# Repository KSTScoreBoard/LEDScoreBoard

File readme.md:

# LED得点掲示板 2023ver.

# 準備するもの
- 電源装置(DC 40V / 300W程度) x4
- 制御基板 x4
- 制御基板用フック x4
- ACアダプタ(5V) x4
- LEDパネル x12
- 電源ケーブル x4
- Wi-Fiアクセスポイント(Windowsのモバイルホットスポット/携帯のテザリング　等) x1
- 操作用端末(Chromeブラウザが動けばOK) x1

# 準備
## 電源
長い間電源を使っていなかった場合は、LEDに繋ぐ前に電源の電圧が39~40Vの範囲にあるかをテスターを使って確認してください。  

## Wi-Fiアクセスポイント
Windowsのモバイルホットスポット/携帯のテザリングとうで制御基板が接続するためのアクセスポイントを用意してください。

# 組み立て
1. 各ブロックLEDパネル3枚を窓とアルミの柱の間に入れて固定する
2. 真ん中のパネル付近に制御基板を取り付ける。このとき基板裏のファンがケーブル等と干渉しないように注意する
3. 制御基板とLEDパネルを接続する
4. 電源装置と制御基板を接続する（電源はまだ入れない）

# 起動
1. 制御基板にACアダプタを接続する
2. 制御基板の起動とネットワーク接続を確認する。(auth ok,ready)と表示されていればOK
3. 電源装置とコンセントを接続する。　※コンセントは2系統から分割して電源をとること。
4. 制御アプリで「送信」を押す or 制御基板のボタンを押す　でLEDが点灯することを確認する
5. 得点「888」を表示してすべてのセグメントが点灯していることを確認する

# 操作

## 送信

各操作を行ったら送信ボタンを押してデータをLEDパネルへ送信してください。4つのブロックの状態を一斉に変更します。

## 得点を変える

各桁の上下にある「＋」、「－」ボタンで数字を操作して目的の得点に変更出来たら最後にページ上部の「送信」ボタンを押してください。また、複数のブロックの得点を同時に変更する場合は各ブロックの得点を操作し終わってから最後にまとめて「送信」を押してください。

## 明るさを変える

スライドバー（8段階）を一番左で消灯、一番右で明るさ最大です。

## 得点を隠す

得点発表時などに得点を隠すには「非表示」ボタンを使用します。3つのボタンが各桁に対応しており、推すとグレーになります。ボタンがグレーになった状態で「送信」することで非表示が押されてる桁は数字を隠せます。

# 詳細
## Wi-Fiについて
Wi-Fiは使用しているマイコンの関係で2.4Ghz帯を使用する必要があります。校舎に飛んでいるWi-FIは5Ghzのため、Windwosの「モバイルホットスポット」等の機能を使って2.4Ghzネットワークを用意してください。SSIDとパスワードは任意で、変更する場合はマイコンのプログラムも変更してください。

## マイコンの設定情報について
通信に使用するIDとWi-Fi設定はメインのプログラムとは別のファイル **defines.h** に書き込まれています。プログラムを変更する場合は以下にソースコードがあるのでコピーしてください
<details><summary>defines.h</summary>

```
#ifndef defines_h
#define defines_h

#if !( defined(ESP8266) ||  defined(ESP32) )
#error This code is intended to run on the ESP32 platform! Please check your Tools->Board setting.
#elif ( ARDUINO_ESP32S2_DEV || ARDUINO_FEATHERS2 || ARDUINO_ESP32S2_THING_PLUS || ARDUINO_MICROS2 || \
        ARDUINO_METRO_ESP32S2 || ARDUINO_MAGTAG29_ESP32S2 || ARDUINO_FUNHOUSE_ESP32S2 || \
        ARDUINO_ADAFRUIT_FEATHER_ESP32S2_NOPSRAM )
#define BOARD_TYPE      "ESP32-S2"
#elif ( ARDUINO_ESP32C3_DEV )
#warning Using ESP32-C3 boards
#define BOARD_TYPE      "ESP32-C3"
#else
#define BOARD_TYPE      "ESP32"
#endif

#ifndef BOARD_NAME
  #define BOARD_NAME    BOARD_TYPE
#endif

#define DEBUG_WEBSOCKETS_PORT     Serial
// Debug Level from 0 to 4
#define _WEBSOCKETS_LOGLEVEL_     3

const char* ssid = "your ssid";          //Enter SSID
const char* password = "your passsword"; //Enter Password

const String identification = "1";       //Enter ID

// Deprecated echo.websocket.org to be replaced or it won't work
const char* websockets_connection_string = "wss://echo.websocket.org/"; //Enter server adress

// KH, This certificate was updated 15.04.2021,
// Issued on Mar 15th 2021, expired on June 13th 2021
const char echo_org_ssl_ca_cert[] PROGMEM = \
                                            "-----BEGIN CERTIFICATE-----\n" \
                                            "MIIEZTCCA02gAwIBAgIQQAF1BIMUpMghjISpDBbN3zANBgkqhkiG9w0BAQsFADA/\n" \
                                            "MSQwIgYDVQQKExtEaWdpdGFsIFNpZ25hdHVyZSBUcnVzdCBDby4xFzAVBgNVBAMT\n" \
                                            "DkRTVCBSb290IENBIFgzMB4XDTIwMTAwNzE5MjE0MFoXDTIxMDkyOTE5MjE0MFow\n" \
                                            "MjELMAkGA1UEBhMCVVMxFjAUBgNVBAoTDUxldCdzIEVuY3J5cHQxCzAJBgNVBAMT\n" \
                                            "AlIzMIIBIjANBgkqhkiG9w0BAQEFAAOCAQ8AMIIBCgKCAQEAuwIVKMz2oJTTDxLs\n" \
                                            "jVWSw/iC8ZmmekKIp10mqrUrucVMsa+Oa/l1yKPXD0eUFFU1V4yeqKI5GfWCPEKp\n" \
                                            "Tm71O8Mu243AsFzzWTjn7c9p8FoLG77AlCQlh/o3cbMT5xys4Zvv2+Q7RVJFlqnB\n" \
                                            "U840yFLuta7tj95gcOKlVKu2bQ6XpUA0ayvTvGbrZjR8+muLj1cpmfgwF126cm/7\n" \
                                            "gcWt0oZYPRfH5wm78Sv3htzB2nFd1EbjzK0lwYi8YGd1ZrPxGPeiXOZT/zqItkel\n" \
                                            "/xMY6pgJdz+dU/nPAeX1pnAXFK9jpP+Zs5Od3FOnBv5IhR2haa4ldbsTzFID9e1R\n" \
                                            "oYvbFQIDAQABo4IBaDCCAWQwEgYDVR0TAQH/BAgwBgEB/wIBADAOBgNVHQ8BAf8E\n" \
                                            "BAMCAYYwSwYIKwYBBQUHAQEEPzA9MDsGCCsGAQUFBzAChi9odHRwOi8vYXBwcy5p\n" \
                                            "ZGVudHJ1c3QuY29tL3Jvb3RzL2RzdHJvb3RjYXgzLnA3YzAfBgNVHSMEGDAWgBTE\n" \
                                            "p7Gkeyxx+tvhS5B1/8QVYIWJEDBUBgNVHSAETTBLMAgGBmeBDAECATA/BgsrBgEE\n" \
                                            "AYLfEwEBATAwMC4GCCsGAQUFBwIBFiJodHRwOi8vY3BzLnJvb3QteDEubGV0c2Vu\n" \
                                            "Y3J5cHQub3JnMDwGA1UdHwQ1MDMwMaAvoC2GK2h0dHA6Ly9jcmwuaWRlbnRydXN0\n" \
                                            "LmNvbS9EU1RST09UQ0FYM0NSTC5jcmwwHQYDVR0OBBYEFBQusxe3WFbLrlAJQOYf\n" \
                                            "r52LFMLGMB0GA1UdJQQWMBQGCCsGAQUFBwMBBggrBgEFBQcDAjANBgkqhkiG9w0B\n" \
                                            "AQsFAAOCAQEA2UzgyfWEiDcx27sT4rP8i2tiEmxYt0l+PAK3qB8oYevO4C5z70kH\n" \
                                            "ejWEHx2taPDY/laBL21/WKZuNTYQHHPD5b1tXgHXbnL7KqC401dk5VvCadTQsvd8\n" \
                                            "S8MXjohyc9z9/G2948kLjmE6Flh9dDYrVYA9x2O+hEPGOaEOa1eePynBgPayvUfL\n" \
                                            "qjBstzLhWVQLGAkXXmNs+5ZnPBxzDJOLxhF2JIbeQAcH5H0tZrUlo5ZYyOqA7s9p\n" \
                                            "O5b85o3AM/OJ+CktFBQtfvBhcJVd9wvlwPsk+uyOy2HI7mNxKKgsBTt375teA2Tw\n" \
                                            "UdHkhVNcsAKX1H7GNNLOEADksd86wuoXvg==\n" \
                                            "-----END CERTIFICATE-----\n";

#endif      //defines_h

```

</details>

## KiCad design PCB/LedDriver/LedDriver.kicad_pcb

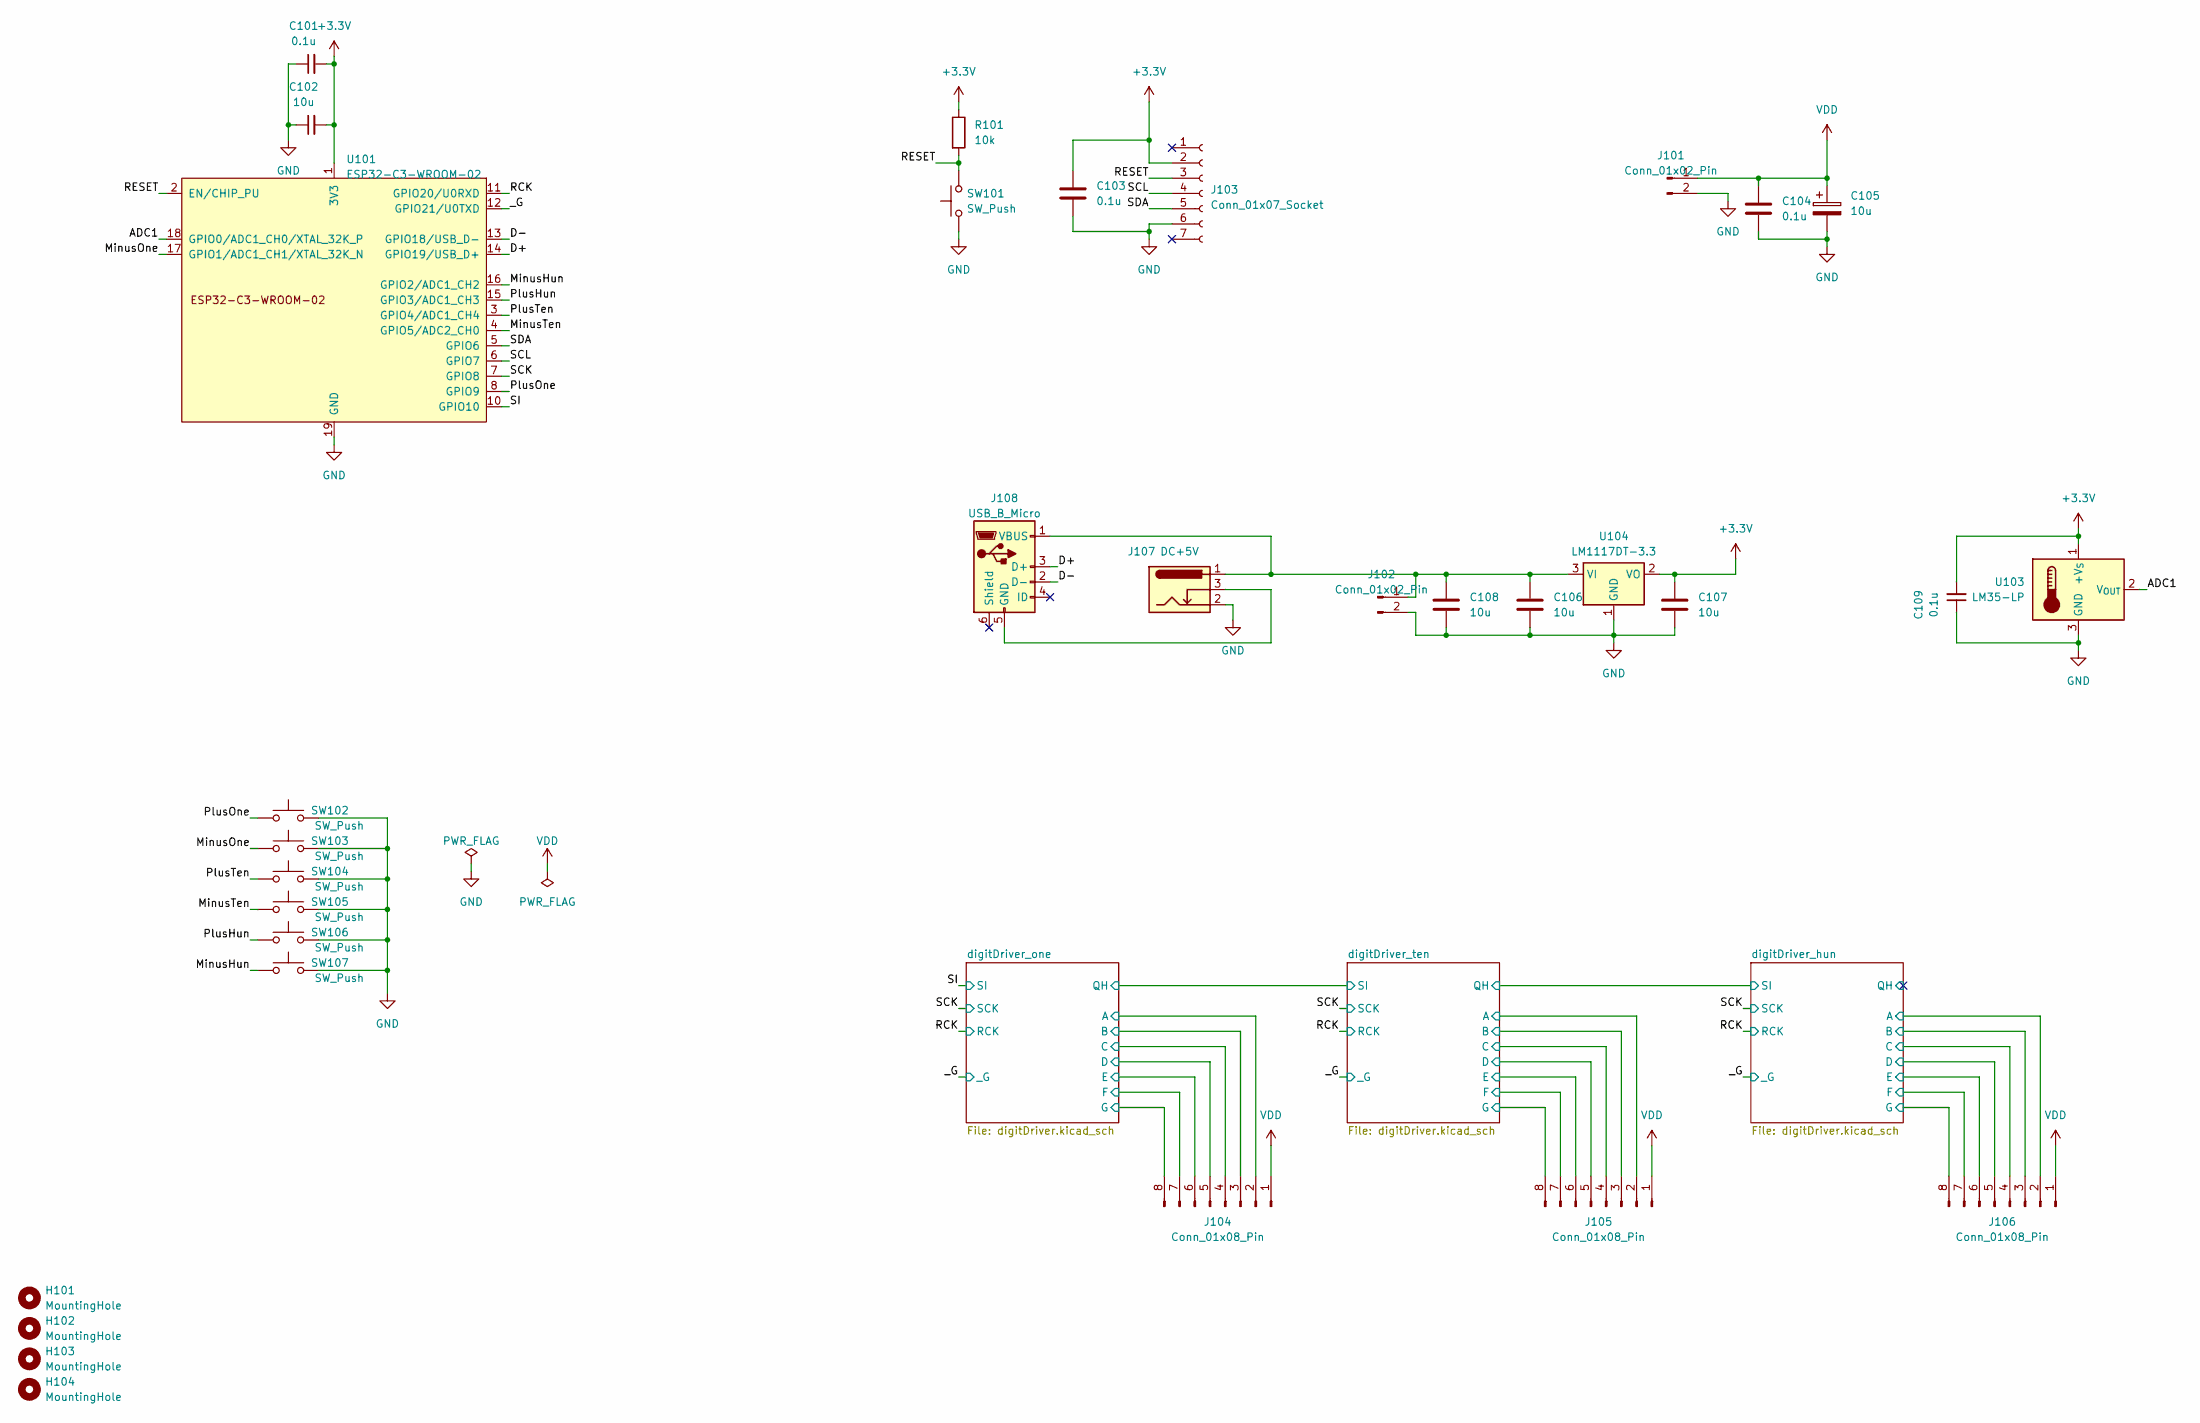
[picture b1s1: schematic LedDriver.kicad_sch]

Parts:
C101, C103, C109: 0.1u; C_0603_1608Metric
C102, C106, C107, C108: 10u; C_0603_1608Metric
C104: 0.1u; C_1206_3216Metric
C105: 10u; CP_Radial_D10.0mm_P5.00mm
H101, H102, H103, H104: MountingHole; MountingHole_3.2mm_M3
J101: Conn_01x02_Pin; JST_VH_B2P-VH_1x02_P3.96mm_Vertical
J102: Conn_01x02_Pin; JST_XH_B2B-XH-A_1x02_P2.50mm_Vertical
J103: Conn_01x07_Socket; PinSocket_1x07_P2.54mm_Vertical
J104, J105, J106: Conn_01x08_Pin; JST_VH_B8P-VH_1x08_P3.96mm_Vertical
J107: DC+5V; BarrelJack_CUI_PJ-102AH_Horizontal
J108: USB_B_Micro; ZX62R-B-5P30
R101: 10k; R_0603_1608Metric
SW101, SW102, SW103, SW104, SW105, SW106, SW107: SW_Push; SW_SPST_B3S-1000
U101: ESP32-C3-WROOM-02
U103: LM35-LP; TO-92_Inline
U104: LM1117DT-3.3; SOT-223-3_TabPin2

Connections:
+3.3V: C101.2, C102.2, C103.1, C107.1, C109.2, J103.2, R101.1, U101.1 (3V3), U103.1 (+V_{S}), U104.2 (VO); also elsewhere on the board
/ADC1: U101.18 (GPIO0/ADC1_CH0/XTAL_32K_P), U103.2 (V_{OUT})
/D+: J108.3 (D+), U101.14 (GPIO19/USB_D+)
/D-: J108.2 (D-), U101.13 (GPIO18/USB_D-)
/MinusHun: SW107.1, U101.16 (GPIO2/ADC1_CH2)
/MinusOne: SW103.1, U101.17 (GPIO1/ADC1_CH1/XTAL_32K_N)
/MinusTen: SW105.1, U101.4 (GPIO5/ADC2_CH0)
/PlusHun: SW106.1, U101.15 (GPIO3/ADC1_CH3)
/PlusOne: SW102.1, U101.8 (GPIO9)
/PlusTen: SW104.1, U101.3 (GPIO4/ADC1_CH4)
/RCK: U101.11 (GPIO20/U0RXD); also elsewhere on the board
/RESET: J103.3, R101.2, SW101.2, U101.2 (EN/CHIP_PU)
/SCK: U101.7 (GPIO8); also elsewhere on the board
/SCL: J103.4, U101.6 (GPIO7)
/SDA: J103.5, U101.5 (GPIO6)
/SI: U101.10 (GPIO10); also elsewhere on the board
/_G: U101.12 (GPIO21/U0TXD); also elsewhere on the board
/digitDriver_hun/A: J106.2; also elsewhere on the board
/digitDriver_hun/B: J106.3; also elsewhere on the board
/digitDriver_hun/C: J106.4; also elsewhere on the board
/digitDriver_hun/D: J106.5; also elsewhere on the board
/digitDriver_hun/E: J106.6; also elsewhere on the board
/digitDriver_hun/F: J106.7; also elsewhere on the board
/digitDriver_hun/G: J106.8; also elsewhere on the board
/digitDriver_one/A: J104.2; also elsewhere on the board
/digitDriver_one/B: J104.3; also elsewhere on the board
/digitDriver_one/C: J104.4; also elsewhere on the board
/digitDriver_one/D: J104.5; also elsewhere on the board
/digitDriver_one/E: J104.6; also elsewhere on the board
/digitDriver_one/F: J104.7; also elsewhere on the board
/digitDriver_one/G: J104.8; also elsewhere on the board
/digitDriver_ten/A: J105.2; also elsewhere on the board
/digitDriver_ten/B: J105.3; also elsewhere on the board
/digitDriver_ten/C: J105.4; also elsewhere on the board
/digitDriver_ten/D: J105.5; also elsewhere on the board
/digitDriver_ten/E: J105.6; also elsewhere on the board
/digitDriver_ten/F: J105.7; also elsewhere on the board
/digitDriver_ten/G: J105.8; also elsewhere on the board
GND: C101.1, C102.1, C103.2, C104.2, C105.2, C106.2, C107.2, C108.2, C109.1, J101.2, J102.2, J103.6, J107.2, SW101.1, SW102.2, SW103.2, SW104.2, SW105.2, SW106.2, SW107.2, U101.9 (GND), U101.19 (GND), U103.3 (GND), U104.1 (GND); also elsewhere on the board
unnamed: C106.1, C108.1, J102.1, J107.1, J108.1 (VBUS), U104.3 (VI)
unnamed: J107.3, J108.5 (GND)
VDD: C104.1, C105.1, J101.1, J104.1, J105.1, J106.1

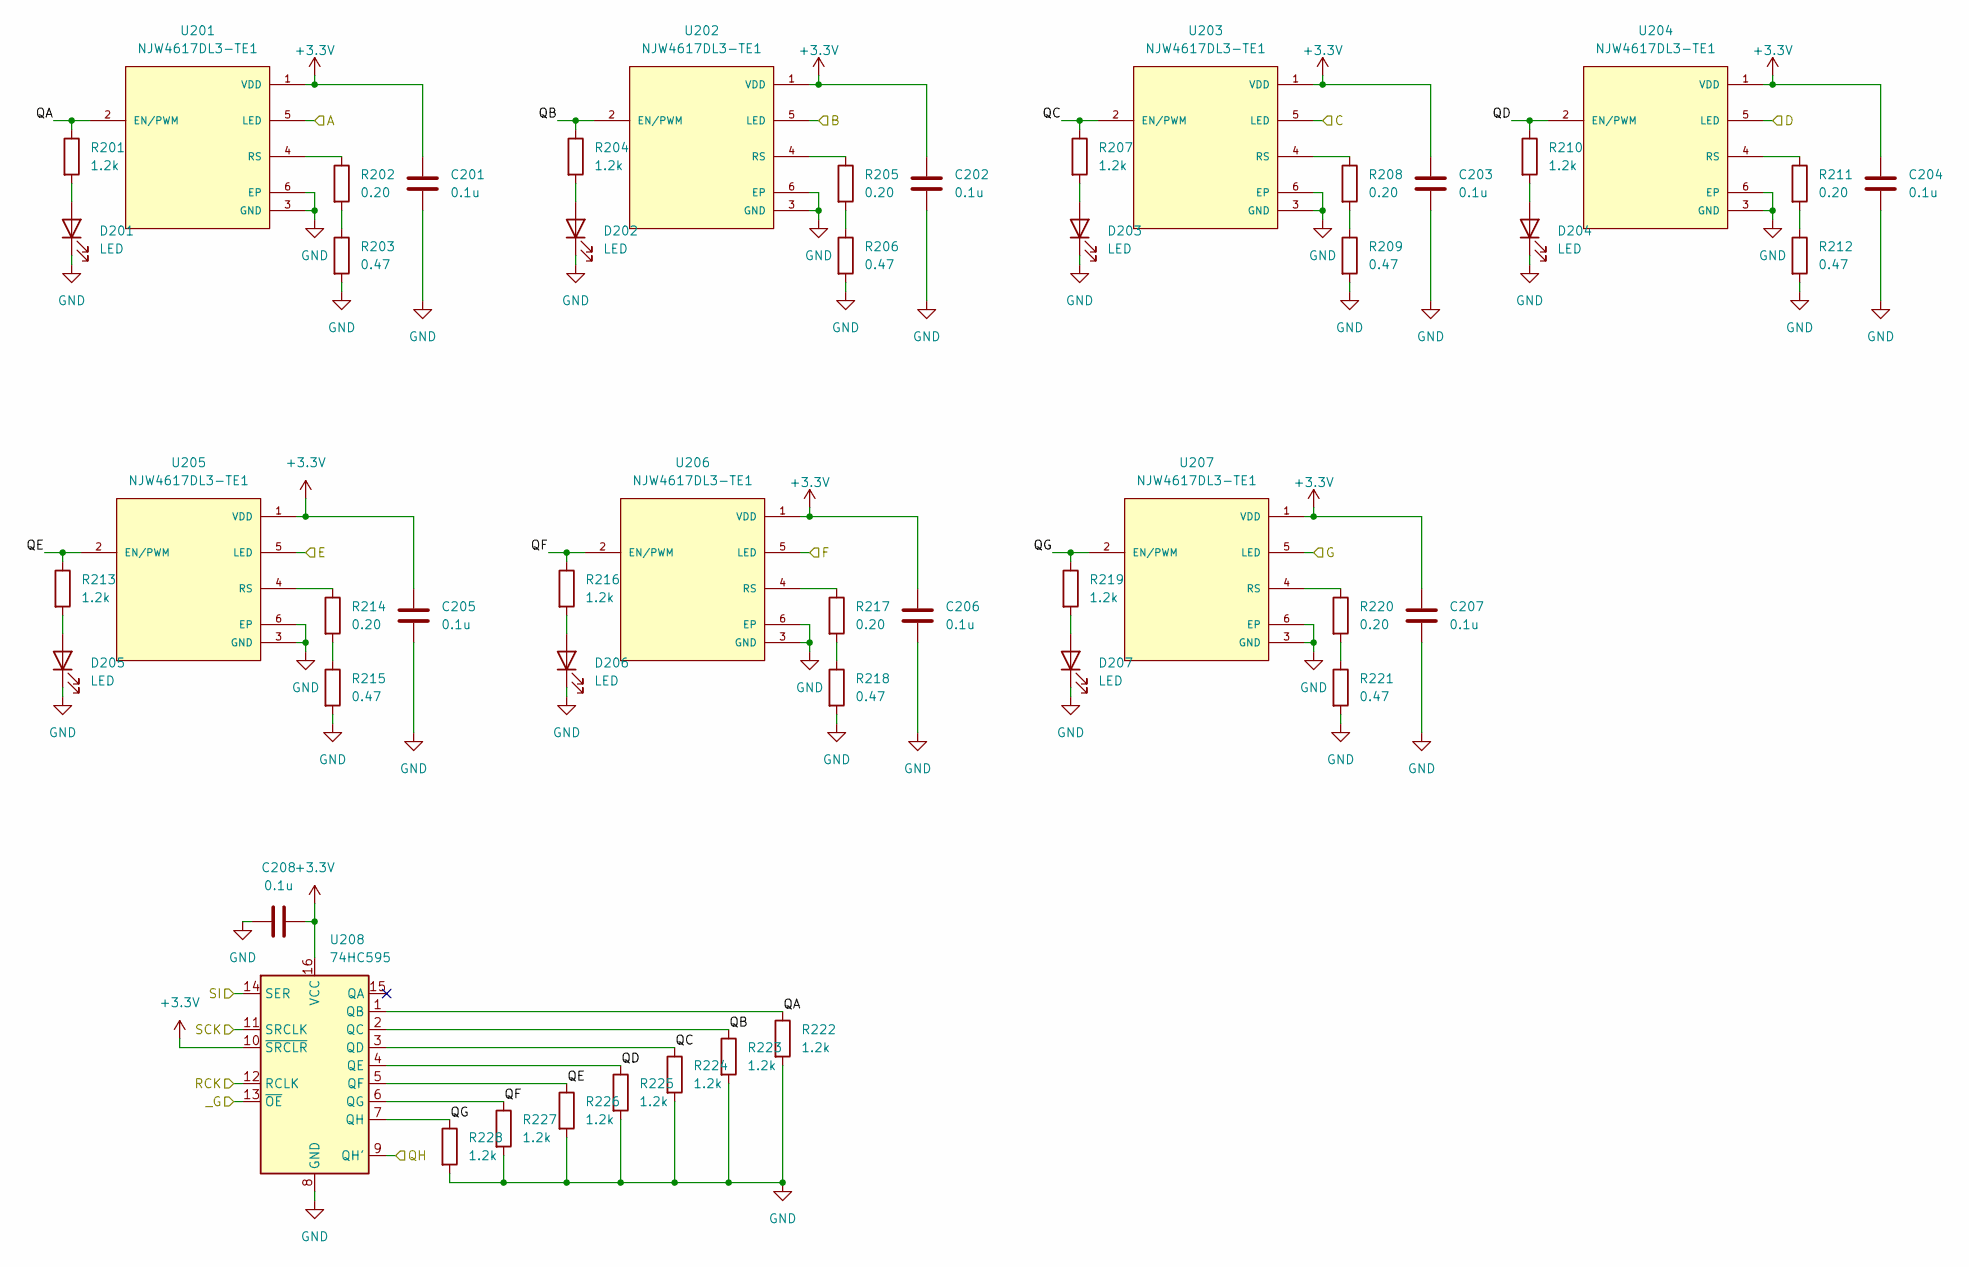
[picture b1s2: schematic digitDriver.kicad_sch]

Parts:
C201, C202, C203, C204, C205, C206, C207, C208: 0.1u; C_0603_1608Metric
D201, D202, D203, D204, D205, D206, D207: LED; LED_0603_1608Metric
R201, R204, R207, R210, R213, R216, R219, R222, R223, R224, R225, R226, R227, R228: 1.2k; R_0603_1608Metric
R202, R205, R208, R211, R214, R217, R220: 0.20; R_Axial_DIN0207_L6.3mm_D2.5mm_P10.16mm_Horizontal
R203, R206, R209, R212, R215, R218, R221: 0.47; R_Axial_DIN0207_L6.3mm_D2.5mm_P10.16mm_Horizontal
U201, U202, U203, U204, U205, U206, U207: NJW4617DL3-TE1; DPAK127P968X238-6N; PARTREV 2017-05-11
U208: 74HC595; SOIC-16W_5.3x10.2mm_P1.27mm

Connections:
+3.3V: C201.1, C202.1, C203.1, C204.1, C205.1, C206.1, C207.1, C208.2, U201.1 (VDD), U202.1 (VDD), U203.1 (VDD), U204.1 (VDD), U205.1 (VDD), U206.1 (VDD), U207.1 (VDD), U208.10 (~SRCLR), U208.16 (VCC); also elsewhere on the board
/RCK: U208.12 (RCLK); also elsewhere on the board
/SCK: U208.11 (SRCLK); also elsewhere on the board
/SI: U208.14 (SER); also elsewhere on the board
/_G: U208.13 (~OE); also elsewhere on the board
/digitDriver_one/A: U201.5 (LED); also elsewhere on the board
/digitDriver_one/B: U202.5 (LED); also elsewhere on the board
/digitDriver_one/C: U203.5 (LED); also elsewhere on the board
/digitDriver_one/D: U204.5 (LED); also elsewhere on the board
/digitDriver_one/E: U205.5 (LED); also elsewhere on the board
/digitDriver_one/F: U206.5 (LED); also elsewhere on the board
/digitDriver_one/G: U207.5 (LED); also elsewhere on the board
/digitDriver_one/QA: R201.1, R222.1, U201.2 (EN/PWM), U208.1 (QB)
/digitDriver_one/QB: R204.1, R223.1, U202.2 (EN/PWM), U208.2 (QC)
/digitDriver_one/QC: R207.1, R224.1, U203.2 (EN/PWM), U208.3 (QD)
/digitDriver_one/QD: R210.1, R225.1, U204.2 (EN/PWM), U208.4 (QE)
/digitDriver_one/QE: R213.1, R226.1, U205.2 (EN/PWM), U208.5 (QF)
/digitDriver_one/QF: R216.1, R227.1, U206.2 (EN/PWM), U208.6 (QG)
/digitDriver_one/QG: R219.1, R228.1, U207.2 (EN/PWM), U208.7 (QH)
/digitDriver_one/QH: U208.9 (QH'); also elsewhere on the board
GND: C201.2, C202.2, C203.2, C204.2, C205.2, C206.2, C207.2, C208.1, D201.1 (K), D202.1 (K), D203.1 (K), D204.1 (K), D205.1 (K), D206.1 (K), D207.1 (K), R203.2, R206.2, R209.2, R212.2, R215.2, R218.2, R221.2, R222.2, R223.2, R224.2, R225.2, R226.2, R227.2, R228.2, U201.3 (GND), U201.6 (EP), U202.3 (GND), U202.6 (EP), U203.3 (GND), U203.6 (EP), U204.3 (GND), U204.6 (EP), U205.3 (GND), U205.6 (EP), U206.3 (GND), U206.6 (EP), U207.3 (GND), U207.6 (EP), U208.8 (GND); also elsewhere on the board
unnamed: D201.2 (A), R201.2
unnamed: D202.2 (A), R204.2
unnamed: D203.2 (A), R207.2
unnamed: D204.2 (A), R210.2
unnamed: D205.2 (A), R213.2
unnamed: D206.2 (A), R216.2
unnamed: D207.2 (A), R219.2
unnamed: R202.2, R203.1
unnamed: R205.2, R206.1
unnamed: R208.2, R209.1
unnamed: R211.2, R212.1
unnamed: R214.2, R215.1
unnamed: R217.2, R218.1
unnamed: R220.2, R221.1
unnamed: R202.1, U201.4 (RS)
unnamed: R205.1, U202.4 (RS)
unnamed: R208.1, U203.4 (RS)
unnamed: R211.1, U204.4 (RS)
unnamed: R214.1, U205.4 (RS)
unnamed: R217.1, U206.4 (RS)
unnamed: R220.1, U207.4 (RS)

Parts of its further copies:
C301, C302, C303, C304, C305, C306, C307, C308, C401, C402, C403, C404, C405, C406, C407, C408: 0.1u; C_0603_1608Metric
D301, D302, D303, D304, D305, D306, D307, D401, D402, D403, D404, D405, D406, D407: LED; LED_0603_1608Metric
R301, R304, R307, R310, R313, R316, R319, R322, R323, R324, R325, R326, R327, R328, R401, R404, R407, R410, R413, R416, R419, R422, R423, R424, R425, R426, R427, R428: 1.2k; R_0603_1608Metric
R302, R305, R308, R311, R314, R317, R320, R402, R405, R408, R411, R414, R417, R420: 0.20; R_Axial_DIN0207_L6.3mm_D2.5mm_P10.16mm_Horizontal
R303, R306, R309, R312, R315, R318, R321, R403, R406, R409, R412, R415, R418, R421: 0.47; R_Axial_DIN0207_L6.3mm_D2.5mm_P10.16mm_Horizontal
U301, U302, U303, U304, U305, U306, U307, U401, U402, U403, U404, U405, U406, U407: NJW4617DL3-TE1; DPAK127P968X238-6N; PARTREV 2017-05-11
U308, U408: 74HC595; SOIC-16W_5.3x10.2mm_P1.27mm

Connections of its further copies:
+3.3V: C301.1, C302.1, C303.1, C304.1, C305.1, C306.1, C307.1, C308.2, C401.1, C402.1, C403.1, C404.1, C405.1, C406.1, C407.1, C408.2, U301.1 (VDD), U302.1 (VDD), U303.1 (VDD), U304.1 (VDD), U305.1 (VDD), U306.1 (VDD), U307.1 (VDD), U308.10 (~SRCLR), U308.16 (VCC), U401.1 (VDD), U402.1 (VDD), U403.1 (VDD), U404.1 (VDD), U405.1 (VDD), U406.1 (VDD), U407.1 (VDD), U408.10 (~SRCLR), U408.16 (VCC); also elsewhere on the board
/RCK: U308.12 (RCLK), U408.12 (RCLK); also elsewhere on the board
/SCK: U308.11 (SRCLK), U408.11 (SRCLK); also elsewhere on the board
/_G: U308.13 (~OE), U408.13 (~OE); also elsewhere on the board
/digitDriver_hun/A: U401.5 (LED); also elsewhere on the board
/digitDriver_hun/B: U402.5 (LED); also elsewhere on the board
/digitDriver_hun/C: U403.5 (LED); also elsewhere on the board
/digitDriver_hun/D: U404.5 (LED); also elsewhere on the board
/digitDriver_hun/E: U405.5 (LED); also elsewhere on the board
/digitDriver_hun/F: U406.5 (LED); also elsewhere on the board
/digitDriver_hun/G: U407.5 (LED); also elsewhere on the board
/digitDriver_hun/QA: R401.1, R422.1, U401.2 (EN/PWM), U408.1 (QB)
/digitDriver_hun/QB: R404.1, R423.1, U402.2 (EN/PWM), U408.2 (QC)
/digitDriver_hun/QC: R407.1, R424.1, U403.2 (EN/PWM), U408.3 (QD)
/digitDriver_hun/QD: R410.1, R425.1, U404.2 (EN/PWM), U408.4 (QE)
/digitDriver_hun/QE: R413.1, R426.1, U405.2 (EN/PWM), U408.5 (QF)
/digitDriver_hun/QF: R416.1, R427.1, U406.2 (EN/PWM), U408.6 (QG)
/digitDriver_hun/QG: R419.1, R428.1, U407.2 (EN/PWM), U408.7 (QH)
/digitDriver_hun/QH: U408.9 (QH')
/digitDriver_hun/SI: U308.9 (QH'), U408.14 (SER)
/digitDriver_one/QH: U308.14 (SER); also elsewhere on the board
/digitDriver_ten/A: U301.5 (LED); also elsewhere on the board
/digitDriver_ten/B: U302.5 (LED); also elsewhere on the board
/digitDriver_ten/C: U303.5 (LED); also elsewhere on the board
/digitDriver_ten/D: U304.5 (LED); also elsewhere on the board
/digitDriver_ten/E: U305.5 (LED); also elsewhere on the board
/digitDriver_ten/F: U306.5 (LED); also elsewhere on the board
/digitDriver_ten/G: U307.5 (LED); also elsewhere on the board
/digitDriver_ten/QA: R301.1, R322.1, U301.2 (EN/PWM), U308.1 (QB)
/digitDriver_ten/QB: R304.1, R323.1, U302.2 (EN/PWM), U308.2 (QC)
/digitDriver_ten/QC: R307.1, R324.1, U303.2 (EN/PWM), U308.3 (QD)
/digitDriver_ten/QD: R310.1, R325.1, U304.2 (EN/PWM), U308.4 (QE)
/digitDriver_ten/QE: R313.1, R326.1, U305.2 (EN/PWM), U308.5 (QF)
/digitDriver_ten/QF: R316.1, R327.1, U306.2 (EN/PWM), U308.6 (QG)
/digitDriver_ten/QG: R319.1, R328.1, U307.2 (EN/PWM), U308.7 (QH)
GND: C301.2, C302.2, C303.2, C304.2, C305.2, C306.2, C307.2, C308.1, C401.2, C402.2, C403.2, C404.2, C405.2, C406.2, C407.2, C408.1, D301.1 (K), D302.1 (K), D303.1 (K), D304.1 (K), D305.1 (K), D306.1 (K), D307.1 (K), D401.1 (K), D402.1 (K), D403.1 (K), D404.1 (K), D405.1 (K), D406.1 (K), D407.1 (K), R303.2, R306.2, R309.2, R312.2, R315.2, R318.2, R321.2, R322.2, R323.2, R324.2, R325.2, R326.2, R327.2, R328.2, R403.2, R406.2, R409.2, R412.2, R415.2, R418.2, R421.2, R422.2, R423.2, R424.2, R425.2, R426.2, R427.2, R428.2, U301.3 (GND), U301.6 (EP), U302.3 (GND), U302.6 (EP), U303.3 (GND), U303.6 (EP), U304.3 (GND), U304.6 (EP), U305.3 (GND), U305.6 (EP), U306.3 (GND), U306.6 (EP), U307.3 (GND), U307.6 (EP), U308.8 (GND), U401.3 (GND), U401.6 (EP), U402.3 (GND), U402.6 (EP), U403.3 (GND), U403.6 (EP), U404.3 (GND), U404.6 (EP), U405.3 (GND), U405.6 (EP), U406.3 (GND), U406.6 (EP), U407.3 (GND), U407.6 (EP), U408.8 (GND); also elsewhere on the board
unnamed: D301.2 (A), R301.2
unnamed: D302.2 (A), R304.2
unnamed: D303.2 (A), R307.2
unnamed: D304.2 (A), R310.2
unnamed: D305.2 (A), R313.2
unnamed: D306.2 (A), R316.2
unnamed: D307.2 (A), R319.2
unnamed: D401.2 (A), R401.2
unnamed: D402.2 (A), R404.2
unnamed: D403.2 (A), R407.2
unnamed: D404.2 (A), R410.2
unnamed: D405.2 (A), R413.2
unnamed: D406.2 (A), R416.2
unnamed: D407.2 (A), R419.2
unnamed: R302.2, R303.1
unnamed: R305.2, R306.1
unnamed: R308.2, R309.1
unnamed: R311.2, R312.1
unnamed: R314.2, R315.1
unnamed: R317.2, R318.1
unnamed: R320.2, R321.1
unnamed: R402.2, R403.1
unnamed: R405.2, R406.1
unnamed: R408.2, R409.1
unnamed: R411.2, R412.1
unnamed: R414.2, R415.1
unnamed: R417.2, R418.1
unnamed: R420.2, R421.1
unnamed: R302.1, U301.4 (RS)
unnamed: R305.1, U302.4 (RS)
unnamed: R308.1, U303.4 (RS)
unnamed: R311.1, U304.4 (RS)
unnamed: R314.1, U305.4 (RS)
unnamed: R317.1, U306.4 (RS)
unnamed: R320.1, U307.4 (RS)
unnamed: R402.1, U401.4 (RS)
unnamed: R405.1, U402.4 (RS)
unnamed: R408.1, U403.4 (RS)
unnamed: R411.1, U404.4 (RS)
unnamed: R414.1, U405.4 (RS)
unnamed: R417.1, U406.4 (RS)
unnamed: R420.1, U407.4 (RS)

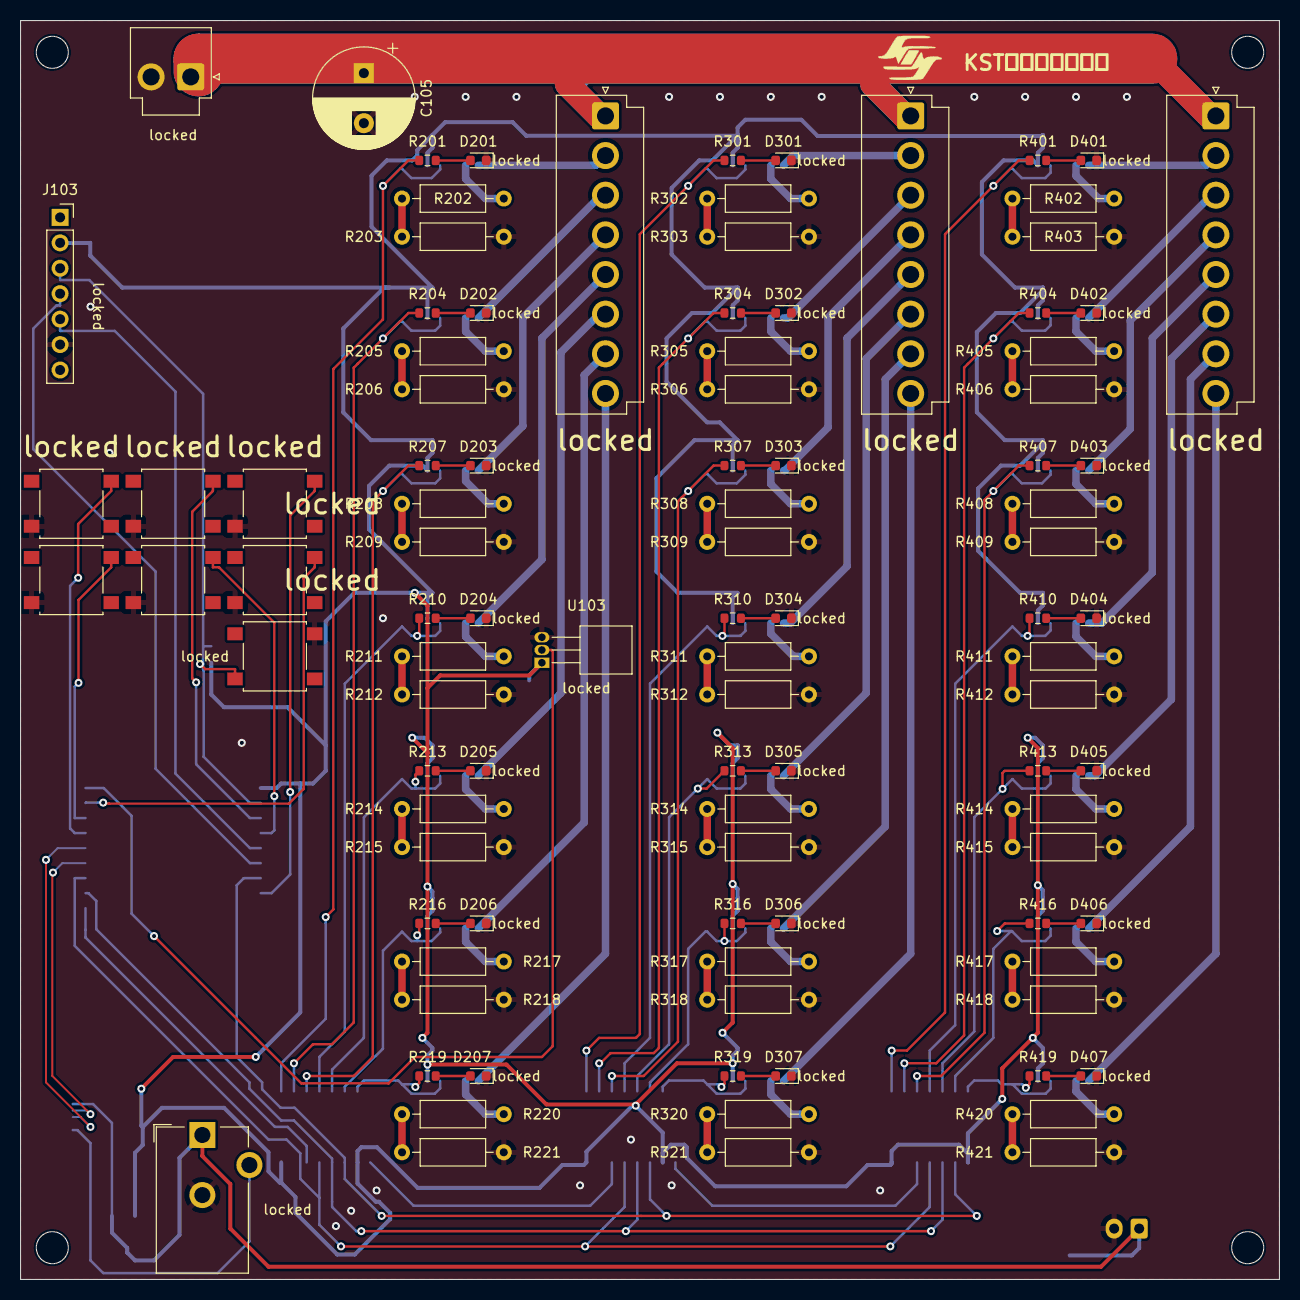
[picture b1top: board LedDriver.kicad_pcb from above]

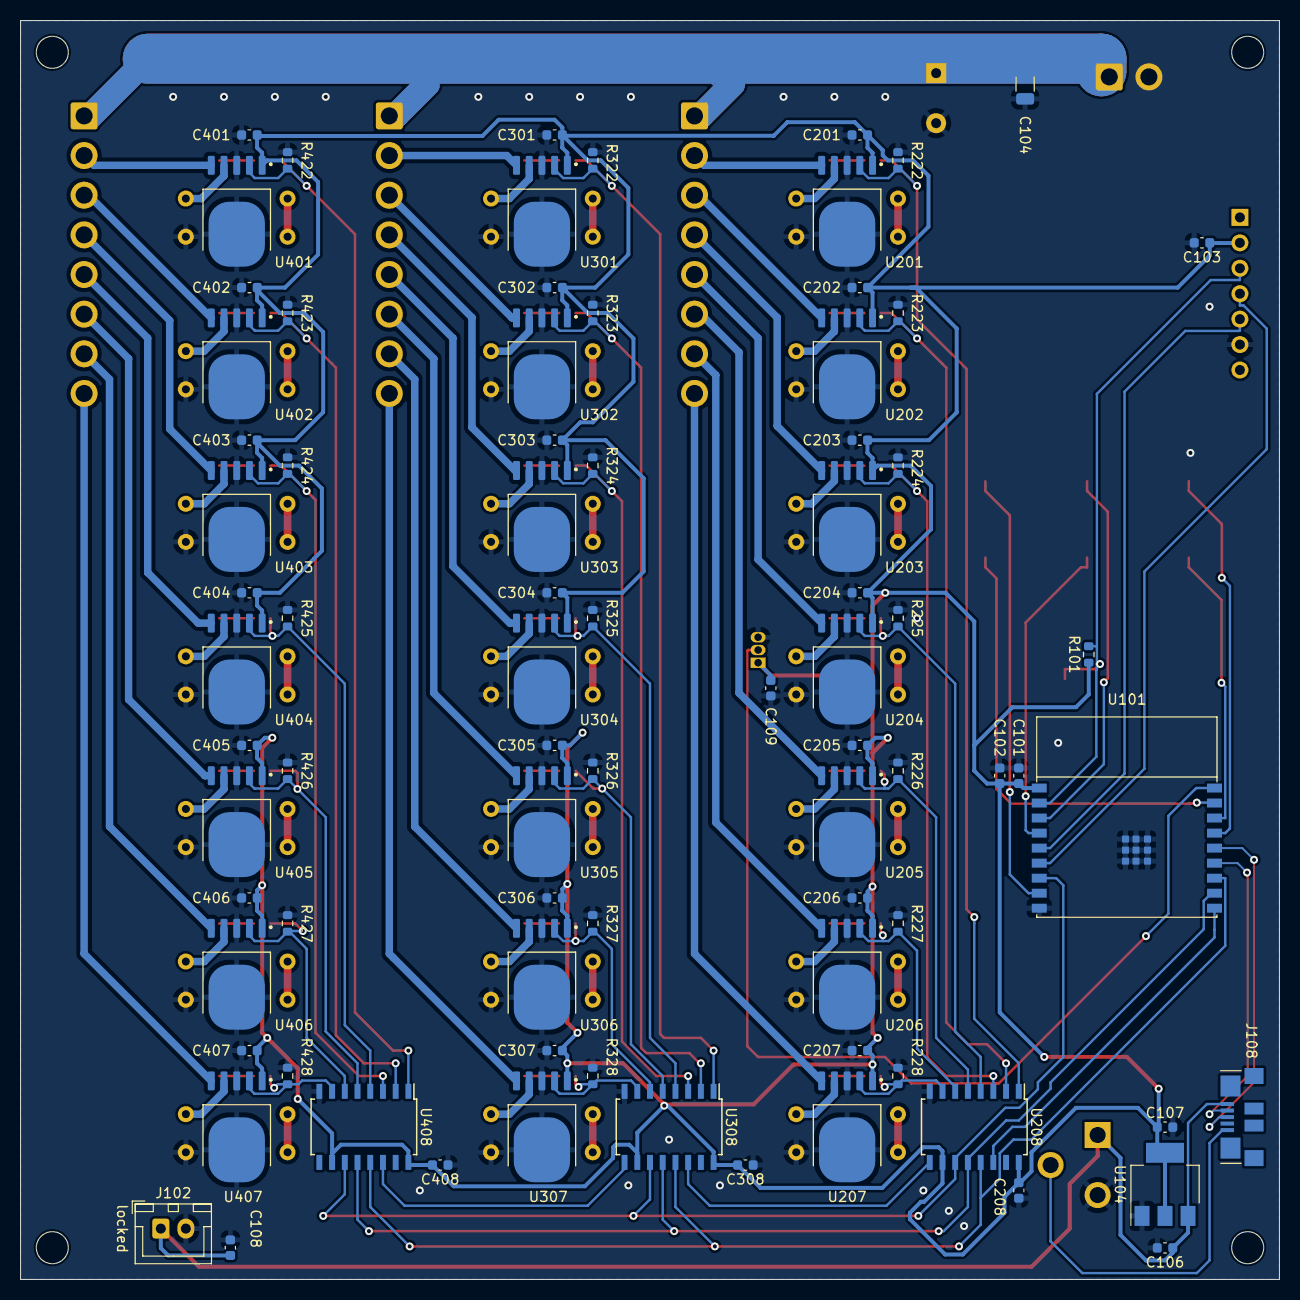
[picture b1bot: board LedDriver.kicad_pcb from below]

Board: 2 copper layers, 125.7 x 125.7 mm, 185 parts (82 on the bottom side), 128 nets.

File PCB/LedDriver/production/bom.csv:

Designator,Footprint,Quantity,Value,LCSC Part #
"C101, C103, C109, C201, C202, C203, C204, C205, C206, C207, C208, C301, C302, C303, C304, C305, C306, C307, C308, C401, C402, C403, C404, C405, C406, C407, C408",0603,27,0.1u,
"C102, C106, C107, C108",0603,4,10u,
C104,1206,1,0.1u,
C105,CP_Radial_D10.0mm_P5.00mm,1,10u,
"D201, D202, D203, D204, D205, D206, D207, D301, D302, D303, D304, D305, D306, D307, D401, D402, D403, D404, D405, D406, D407",0603,21,LED,
"H101, H102, H103, H104",MountingHole_3.2mm_M3,4,MountingHole,
J101,JST_VH_B2P-VH_1x02_P3.96mm_Vertical,1,Conn_01x02_Pin,
J102,JST_XH_B2B-XH-A_1x02_P2.50mm_Vertical,1,Conn_01x02_Pin,
J103,PinSocket_1x07_P2.54mm_Vertical,1,Conn_01x07_Socket,
"J104, J105, J106",JST_VH_B8P-VH_1x08_P3.96mm_Vertical,3,Conn_01x08_Pin,
J107,BarrelJack_CUI_PJ-102AH_Horizontal,1,DC+5V,
J108,ZX62R-B-5P30,1,USB_B_Micro,
R101,0603,1,10k,
"R201, R204, R207, R210, R213, R216, R219, R222, R223, R224, R225, R226, R227, R228, R301, R304, R307, R310, R313, R316, R319, R322, R323, R324, R325, R326, R327, R328, R401, R404, R407, R410, R413, R416, R419, R422, R423, R424, R425, R426, R427, R428",0603,42,1.2k,
"R202, R205, R208, R211, R214, R217, R220, R302, R305, R308, R311, R314, R317, R320, R402, R405, R408, R411, R414, R417, R420",R_Axial_DIN0207_L6.3mm_D2.5mm_P10.16mm_Horizontal,21,0.20,
"R203, R206, R209, R212, R215, R218, R221, R303, R306, R309, R312, R315, R318, R321, R403, R406, R409, R412, R415, R418, R421",R_Axial_DIN0207_L6.3mm_D2.5mm_P10.16mm_Horizontal,21,0.47,
"SW101, SW102, SW103, SW104, SW105, SW106, SW107",SW_SPST_B3S-1000,7,SW_Push,
U101,ESP32-C3-WROOM-02,1,ESP32-C3-WROOM-02,
U103,TO-92_Inline_Horizontal1,1,LM35-LP,
U104,SOT-223-3_TabPin2,1,LM1117DT-3.3,
"U201, U202, U203, U204, U205, U206, U207, U301, U302, U303, U304, U305, U306, U307, U401, U402, U403, U404, U405, U406, U407",DPAK127P968X238-6N,21,NJW4617DL3-TE1,
"U208, U308, U408",SOIC-16W_5.3x10.2mm_P1.27mm,3,74HC595,

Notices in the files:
parts and their libraries:
Copyright 2021 Accelerated Designs. All rights reserved.
